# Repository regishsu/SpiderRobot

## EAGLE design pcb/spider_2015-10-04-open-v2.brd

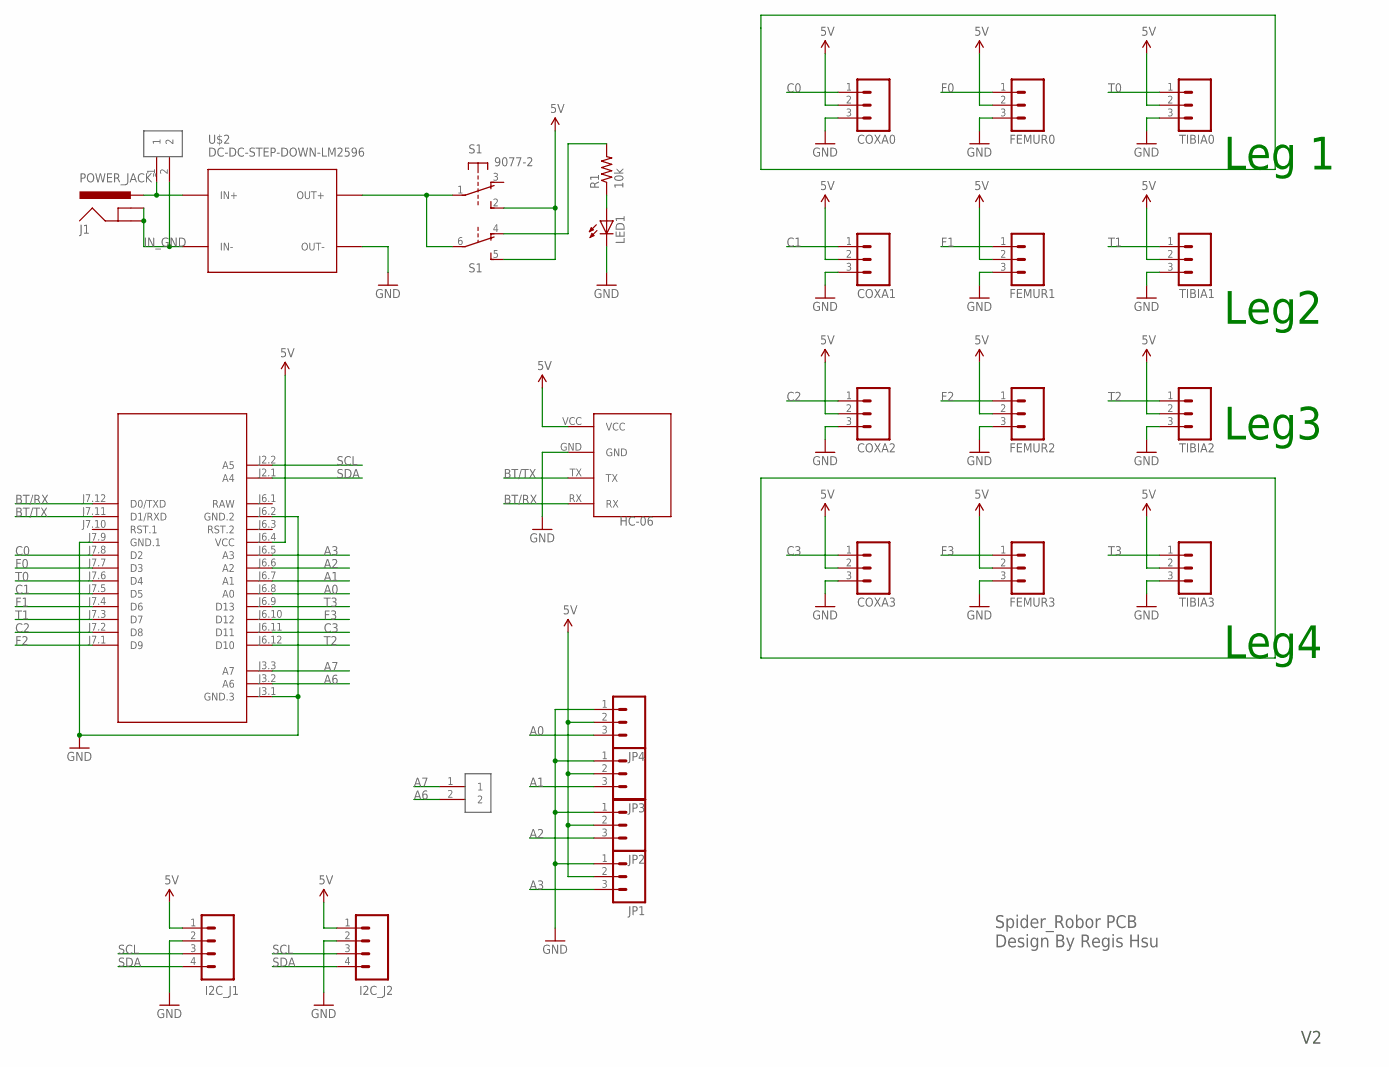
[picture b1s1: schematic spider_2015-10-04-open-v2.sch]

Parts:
COXA0, COXA1, COXA2, COXA3: M03PTH; 1X03
FEMUR0, FEMUR1, FEMUR2, FEMUR3: M03PTH; 1X03
HC-06: BLUETOOTH_BOARDSTANDING; BT_BOARD_FOOTPRINT_STANDING
I2C_J1, I2C_J2: 1X04_HEADER"; 1X04_HEADER
J1: POWER_JACK"; POWER_JACK
JP1, JP2, JP3, JP4: M03PTH; 1X03
LED1: LED3MM; LED
M1: ARDUINO-PRO-MINI-5.0V; ARDUINO-PRO-MINI
R1: 10k; AXIAL-0.4
S1: 9077-2
TIBIA0, TIBIA1, TIBIA2, TIBIA3: M03PTH; 1X03
U$1, U$3: 1X02_HEADER
U$2: DC-DC-STEP-DOWN-LM2596

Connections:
5V: COXA0.2, COXA1.2, COXA2.2, COXA3.2, FEMUR0.2, FEMUR1.2, FEMUR2.2, FEMUR3.2, HC-06.VCC, I2C_J1.1, I2C_J2.1, JP1.2, JP2.2, JP3.2, JP4.2, M1.J6.4 (VCC), S1.2 (S), S1.5 (S), TIBIA0.2, TIBIA1.2, TIBIA2.2, TIBIA3.2
A0: JP4.3, M1.J6.8 (A0)
A1: JP3.3, M1.J6.7 (A1)
A2: JP2.3, M1.J6.6 (A2)
A3: JP1.3, M1.J6.5 (A3)
A6: M1.J3.2 (A6), U$1.2
A7: M1.J3.3 (A7), U$1.1
BT/RX: HC-06.RX, M1.J7.12 (D0/TXD)
BT/TX: HC-06.TX, M1.J7.11 (D1/RXD)
C0: COXA0.1, M1.J7.8 (D2)
C1: COXA1.1, M1.J7.5 (D5)
C2: COXA2.1, M1.J7.2 (D8)
C3: COXA3.1, M1.J6.11 (D11)
F0: FEMUR0.1, M1.J7.7 (D3)
F1: FEMUR1.1, M1.J7.4 (D6)
F2: FEMUR2.1, M1.J7.1 (D9)
F3: FEMUR3.1, M1.J6.10 (D12)
GND: COXA0.3, COXA1.3, COXA2.3, COXA3.3, FEMUR0.3, FEMUR1.3, FEMUR2.3, FEMUR3.3, HC-06.GND, I2C_J1.2, I2C_J2.2, JP1.1, JP2.1, JP3.1, JP4.1, LED1.K (C), M1.J3.1 (GND.3), M1.J6.2 (GND.2), M1.J7.9 (GND.1), TIBIA0.3, TIBIA1.3, TIBIA2.3, TIBIA3.3, U$2.OUT-
IN_GND: J1.GND, J1.GNDBREAK, U$2.IN-, U$3.2
unnamed: J1.PWR, U$2.IN+, U$3.1
unnamed: S1.1, S1.6, U$2.OUT+
unnamed: R1.P$2 (2), S1.4 (O)
unnamed: LED1.A, R1.P$1 (1)
RAW: M1.J6.1 (RAW)
SCL: I2C_J1.3, I2C_J2.3, M1.J2.2 (A5)
SDA: I2C_J1.4, I2C_J2.4, M1.J2.1 (A4)
T0: M1.J7.6 (D4), TIBIA0.1
T1: M1.J7.3 (D7), TIBIA1.1
T2: M1.J6.12 (D10), TIBIA2.1
T3: M1.J6.9 (D13), TIBIA3.1

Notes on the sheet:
Spider_Robor PCB Design By Regis Hsu
Leg 1
Leg4
Leg3
Leg2

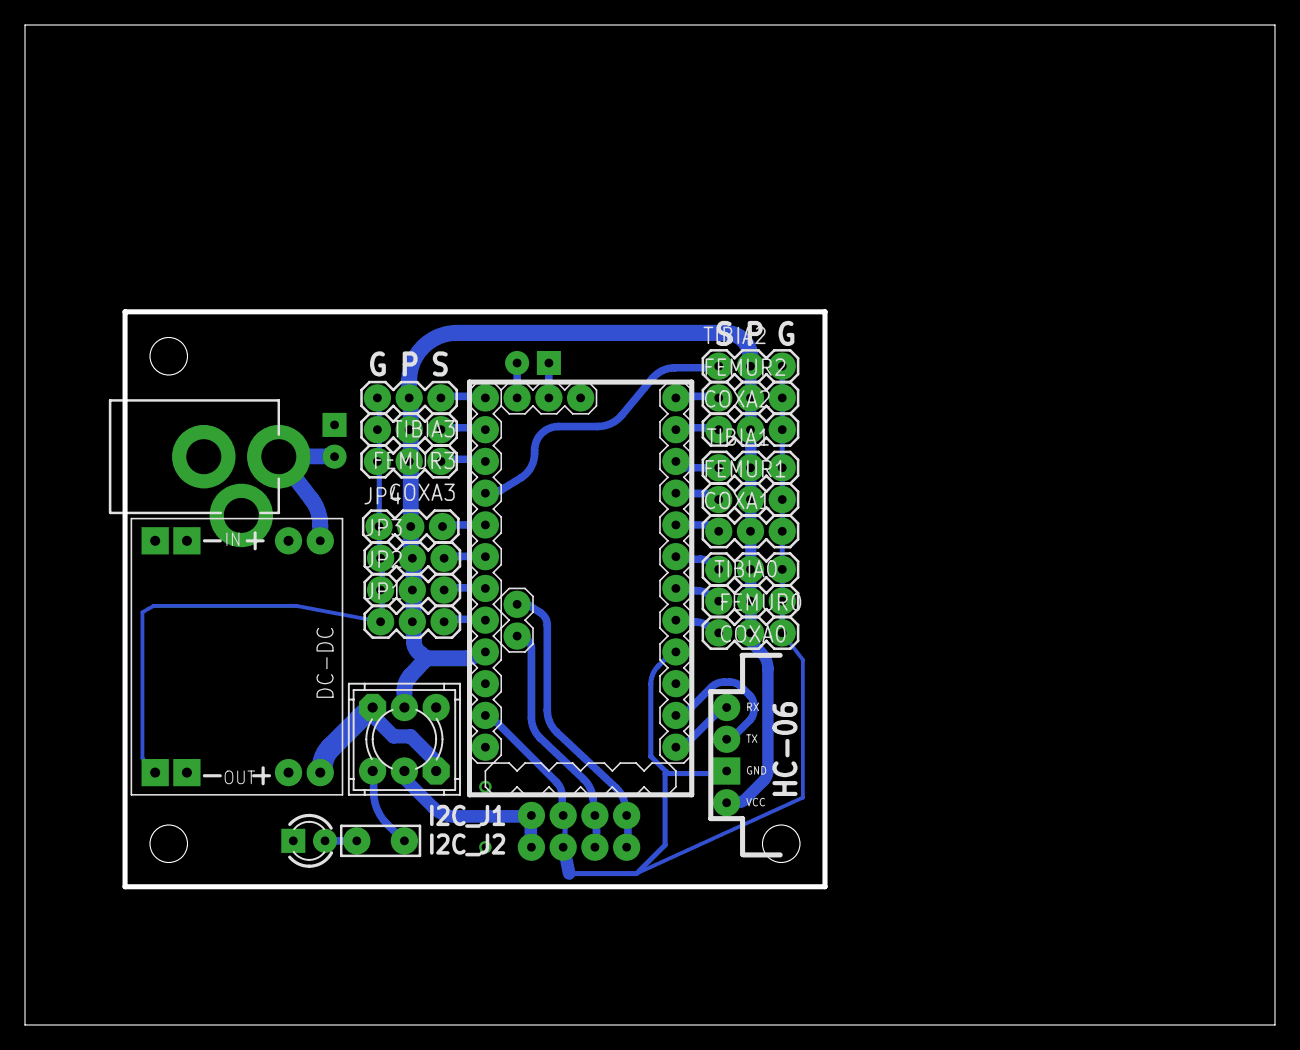
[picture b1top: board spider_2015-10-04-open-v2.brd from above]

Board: 2 copper layers, 99.6 x 79.6 mm, 27 parts (0 on the bottom side), 29 nets.

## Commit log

2015-12-26 init version
